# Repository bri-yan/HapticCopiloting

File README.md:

# HapticCopiloting
Codebase for UBC's ENPH-459 (Engineering Physics) Capstone Project: **Haptic Shared Control**

Demonstrating complex human-robot control through a 1 DOF haptic device featuring a BDC motor control system in live feedback with a virtual environment.

Authors: 
* Gavin Pringle
* Yousif El-Wishahy
* Sayeh Oloumi Yazdi
* Brian Yan

## Important Directories
- twiddlerino: source code for the ESP32 controller, python serial interface, unit tests and test scripts
- sim: MATLAB source code for modelling and simualtion of motor, sensors and controller
- virtual_demos : directory containing virtual demonstrations for shared control, demos implemented in pygame and interface with esp32 controller using the serial interface
- electrical: KiCad pcb project (libraries, schematics and layout) using the twiddlerino hardware, and the KiCad electrical schematic for the test bench

## Contents
 - [Project Overview](#project-overview) 
 - [Firmware Dev Environment](#firmware-dev-environment) 

## Project Overview

When dancing with a partner, forces and torques from each person influence the motion of the other. Each person’s motion is therefore partially controlled by themselves and partially controlled by their partner. 

This is similar to shared control of a robotic system, where the behaviour of a robot changes depending on the stiffness of the environment it is operating in. In our project, we explore shared control on simple robotic devices with the addition of a virtual environment that guides the user on when to give and when to take control.

### Twiddlerino System Diagram

### Control Theory

We have implemented shared control between a human and a robot by shifting between two existing controllers: impedance controllers and admittance controllers. Impedance and admittance controllers both simulate virtual spring-mass-damper systems. By shifting between these two controllers, the combined shared controller can act resistively and prevent changes to its trajectory or act compliantly and allow a person to dictate its trajectory.

### Defined Control Modes

Defined in control_type_t enum in the firmware:

| Control ID               | Description                                                                                                                                                                                                                                          |
|--------------------------|------------------------------------------------------------------------------------------------------------------------------------------------------------------------------------------------------------------------------------------------------|
| no_control               | No actuator control is applied. Only telemetry is report.                                                                                                                                                                                            |
| position                 | Position PID control. Feedback is incremental encoder signal.                                                                                                                                                                                        |
| velocity                 | Velocity PID control. Feedback is rate of change of encoder signal.                                                                                                                                                                                  |
| torque                   | Current PID control to achieve torque control, uses linear relationship between current and torque.<br>Feedback is current sensor measurements.                                                                                                      |
| impedance_spring         | Cascaded controller. Inner loop runs current control with PID. <br>Outer loop applies a spring impedance law to determine desired current. <br>The linear friction torque (scales with velocity) is also accounted for in the impedance control law. |
| impedance_damping        | Similar to imedance_spring but uses imedance damper law to compute current target.                                                                                                                                                                   |
| impedance_spring_damping | Applies spring and damping impedance law. Has the effect of position and velocity impedance control.                                                                                                                                                 |
| impedance_ignore_t_ext   | Applies full impedance law, but ignores external torques.                                                                                                                                                                                            |
| impedance                | Applies full impedance law, and accounts for external torques.<br>External torque is estimated by comparing current measurements to an internal model the motor that estimates control current.                                                      |
| admittance               | Applies full admittance law. This controller is also a cascaded controller.<br>The inner loop runs PID position control.<br>The outer loop runs an impedance control law to compute position.                                                        |

### Virtual Environment
The virtual environment guides the user on when to give and when to take control. The player  must control two twidderinos to ensure both player-controlled ships avoid all obstacles. Ships will automatically avoid asteroids but players must take action to avoid enemy projectiles.

Promoted Behaviour:
* Human-robot collaboration
* Shared common goal
* Awareness of robots actions

### Hardware Architecture

### Firmware Architecure

## Firmware Dev Environment

[Refer to firmware diagram](#firmware-architecture)

Embedded development environment: [Platformio](https://platformio.org/) IDE plugin for VSCode

[Install platformio](https://platformio.org/)

config file: `twiddlerino/platformio.ini`

Directory structure

```bash
├───.pio
│   ├───build
│   └───libdeps
├───include
├───lib
├───python_tests
│   ├───data
│   └───serial_interface
├───src
│   ├───app
│   │   ├───calibration
│   │   ├───control
│   │   └───filter
│   └───drivers
└───test
```

## Serial Commmand & Telemetry Interface

Command and telemetry of the Twiddlerino system is achieved through telemetry and command frames (utf-8 encoded strings) sent over a USB port between the ESP32 and the HOST PC.

The ESP32 devkit has an onboard CP210X USB-to-UART module that converts the USB signal to a UART signal for the UART driver on the ESP32 to handle.

The serial protocol is implemented in C++ on esp32 and Python on Host PC.

[Refer to firmware diagram for details](#firmware-architecture)

### Telemetry Definition

[Serial Studio](https://serial-studio.github.io/), an open source telemetry GUI, is used to record and visualize system data during testing of the controller.

Telemetry frames are defined in a .JSON configuration file per the serial studio standard, see `twiddlerino/serial-studio-dashboard.json`.

Telemetry frame: `"/*TWIDDLERINO_TELEMETRY,%s,%s,...,%s*/"`

The firmware running on the ESP32 periodically sends telemetry strings over a serial port. The python serial protocol recieves the telemetry frames and sends them over a TCP socket to Serial Studio. 

### Command Definition
Several commands are available to set parameters over the serial interface and to control the state of the controller.
**Each command is a newline terminated string.**

`"stop\n"` - Stops controller (telemetry also stops)

`"reset\n"` - Resets controller (configuration reverts to default)

`"reboot\n"` - Reboots the microcontroller! UART driver will not be affected.

`"telemetry_enable\n"` - Enable controller telemetry stream over serial (rate==`TELEMETRY_SAMPLES_PER_LOOP `)

`"telemetry_disable\n"` - Disable controller telemetry stream over serial (rate==`TELEMETRY_SAMPLES_PER_LOOP `)

`"set_pid,<controller_id(string)>,<double>,<double>,<double>,\n"` - Set P, I, and D values of PID controller

`"set_impedance,<controller_id(string)>,<double>,<double>,<double>,\n"` - Set stiffness, damping, and inertia values of impedane/admittance controller

`"set_mode,<controller_id(string)>,<string>,\n"` - Sets control mode, the string values represents an enum. Refer to the `control_type_t` struct definition in `twiddlerino/src/app/control/twid_control.h`.
* modes: `no_control`, `position`, `velocity`, `torque`, `impedance`, `impedance_spring`, `impedance_damping`, `impedance_spring_damping`, `impedance_ignore_t_ext`, `admittance`

`"set_setpoint,<controller_id(string)>,<double>,<double>,<double>,<double>,\n"` - Set position, velocity, acceleration and torque setpoints for the controller. 

`"set_dutycycle,<controller_id(string)>,<int>,\n"` - Sets motor duty cycle directly regardless of controller running.

`"set_telemsamplerate,<controller_id(string)>,<uint>,\n"` - Set telemetry sample rate in terms of (# control loops)/sample. I.e. how many control loops to wait before sending telemetry to serial queue.

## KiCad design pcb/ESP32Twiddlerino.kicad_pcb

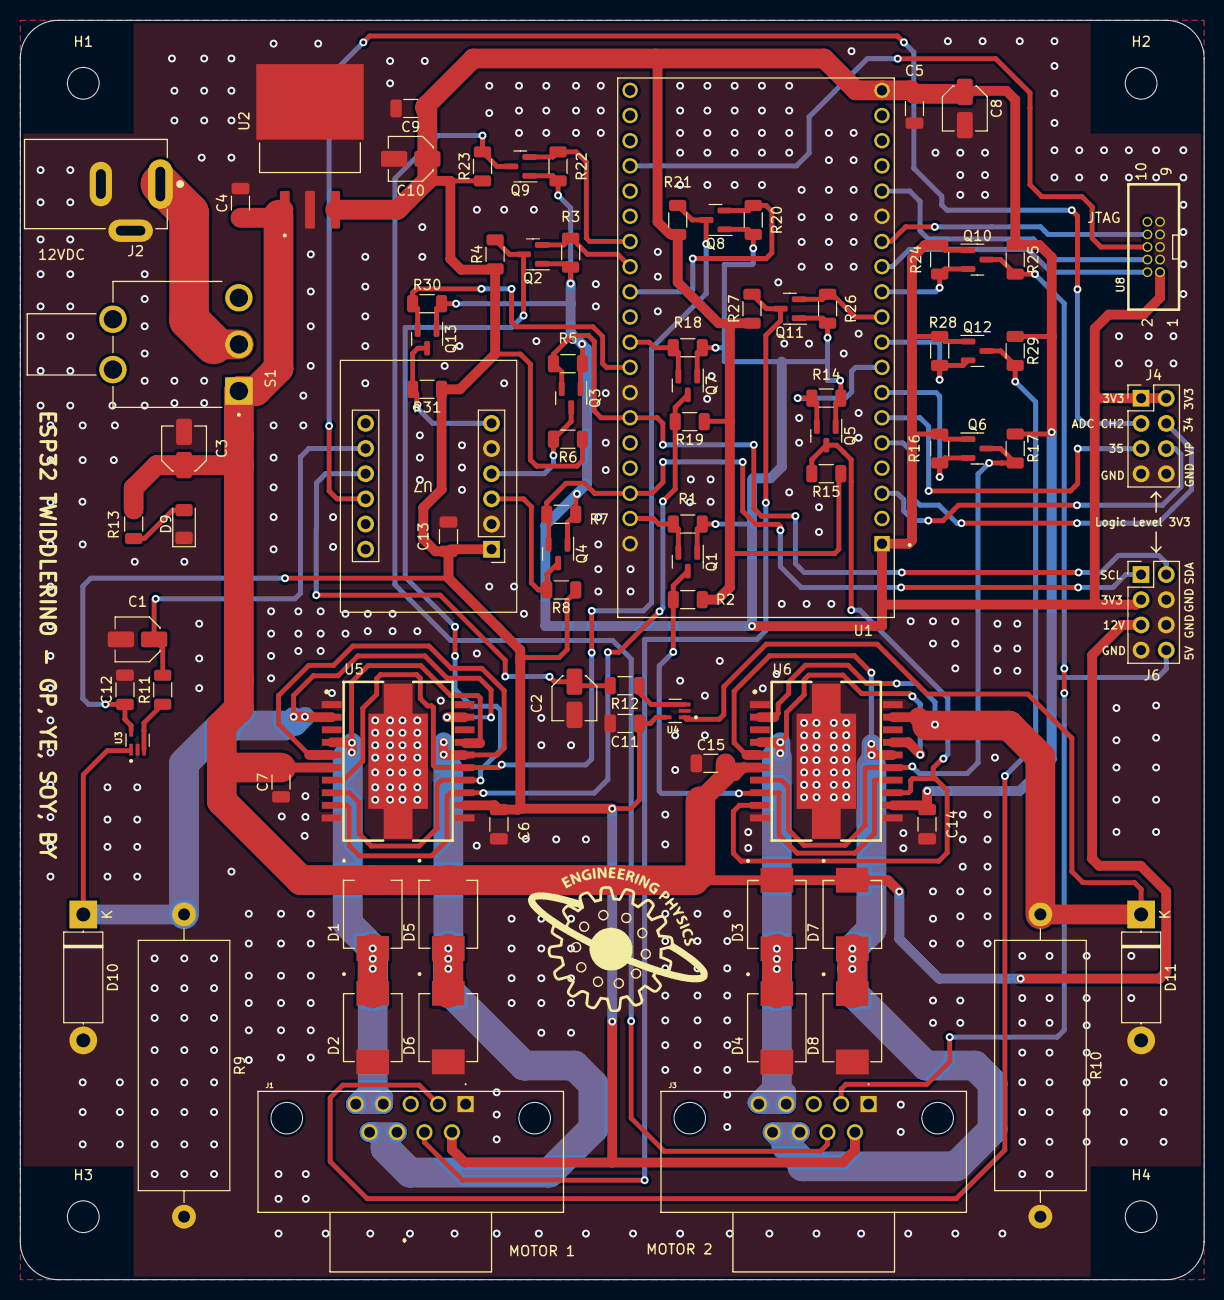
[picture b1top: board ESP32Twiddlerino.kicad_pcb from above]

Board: 2 copper layers, 119.4 x 127.0 mm, 89 parts (0 on the bottom side), 50 nets.

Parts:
.: LOGO
C1, C2: 3.3uF; C_Elec_4x5.4
C3, C8, C10: 10uF; C_Elec_4x5.4
C4: 220nF; C_1206_3216Metric
C5, C6, C7, C9, C11, C12, C13, C14, C15: 100nF; C_1206_3216Metric
D1, D2, D3, D4, D5, D6, D7, D8: RS3A; RS3A-13-F
D9: LED; LED_1206_3216Metric
D10, D11: 1N5337B; D_5W_P12.70mm_Horizontal
H1, H2, H3, H4: MountingHole; MountingHole_3.2mm_M3
J1, J3: 2311765-1; TE_2311765-1
J2: PJ-202AH; CUI_PJ-202AH
J4: Extra_GPIO; PinHeader_2x04_P2.54mm_Vertical
J6: Power_I2C; PinHeader_2x04_P2.54mm_Vertical
Q1, Q2, Q3, Q4, Q5, Q6, Q7, Q8, Q9, Q10, Q11, Q12, Q13: BSS138; SOT-23
R1, R2, R3, R4, R5, R6, R7, R8, R14, R15, R16, R17, R18, R19, R20, R21, R22, R23, R24, R25, R26, R27, R28, R29, R30, R31: 10k; R_1206_3216Metric
R9, R10: 1R; R_Axial_Power_L25.0mm_W9.0mm_P30.48mm
R11, R12: 1k; R_1206_3216Metric
R13: 470R; R_1206_3216Metric
S1: 100SP1T2B4M6QE; SW_100SP1T2B4M6QE
U1: ESP32-DEVKITC-32UE; ESPRESSIF_ESP32-DEVKITC-32UE
U2: LM340S-5.0_NOPB; LM340S-5
U3, U4: OPA347SA_3K; SOT65P210X110-5N
U5, U6: L298P
U7: adafruit_ads1115
U8: 20021511-00010T4LF

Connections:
+3.3V: J4.1, J4.2, J6.3, Q1.1 (G), Q2.1 (G), Q3.1 (G), Q4.1 (G), Q5.1 (G), Q6.1 (G), Q7.1 (G), Q8.1 (G), Q9.1 (G), Q10.1 (G), Q11.1 (G), Q12.1 (G), Q13.1 (G), R1.1, R3.1, R5.1, R7.1, R14.1, R16.1, R18.1, R20.1, R22.1, R24.1, R26.1, R28.1, R30.1, U1.1 (3V3), U8.1
+5V: C5.2, C6.2, C8.1, C9.1, C10.1, C11.1, C12.1, C13.2, C14.2, J1.6, J3.6, J6.8, R2.1, R4.1, R6.1, R8.1, R15.1, R17.1, R19.1, R21.1, R23.1, R25.1, R27.1, R29.1, R31.1, U1.19 (5V), U2.3 (OUT), U3.5 (V+), U4.5 (V+), U5.12 (VSS), U6.12 (VSS), U7.1 (Vin)
+12V: C3.1, C4.1, C7.2, C15.2, D1.C, D3.C, D5.C, D7.C, J6.5, R13.1, S1.1, U2.1 (IN), U5.6 (VS), U6.6 (VS)
ADC_ALRT_H: Q13.3 (D), R31.2, U7.6 (ALRT)
ADC_ALRT_L: Q13.2 (S), R30.2, U1.27 (19)
ESP_SCL_H: Q4.3 (D), R8.2, U7.3 (SCL)
ESP_SCL_L: J6.1, Q4.2 (S), R7.2, U1.22
ESP_SDA_H: Q3.3 (D), R6.2, U7.4 (SDA)
ESP_SDA_L: J6.2, Q3.2 (S), R5.2, U1.25 (21)
Extra_ADC_2: J4.3, U7.10 (A2)
Extra_GPIO_34: J4.4, U1.5 (34)
Extra_GPIO_35: J4.5, U1.6 (35)
Extra_GPIO_VP: J4.6, U1.3 (VP)
GND: C1.2, C2.2, C3.2, C4.2, C5.1, C6.1, C7.1, C8.2, C9.2, C10.2, C11.2, C12.2, C13.1, C14.1, C15.1, D2.A, D4.A, D6.A, D8.A, D9.1 (K), D10.2 (A), D11.2 (A), J1.1, J2.2, J2.3, J3.1, J4.7, J4.8, J6.4, J6.6, J6.7, R9.2, R10.2, U1.14 (GND), U1.20 (GND), U1.26 (GND), U2.2 (GND), U2.4 (GND), U3.2 (V-), U4.2 (V-), U5.1 (GND), U5.10 (GND), U5.11 (GND), U5.20 (GND), U5.21 (PAD), U5.22 (PAD), U5.23 (PAD), U6.1 (GND), U6.10 (GND), U6.11 (GND), U6.20 (GND), U6.21 (PAD), U6.22 (PAD), U6.23 (PAD), U7.2 (GND), U7.5 (ADDR), U8.3, U8.5, U8.7, U8.9
MTCK: U1.15 (13), U8.4
MTDI: U1.13 (12), U8.8
MTDO: U1.35 (15), U8.6
MTMS: U1.12 (14), U8.2
Mot_1_Dir_1_H: Q8.3 (D), R21.2, U5.7 (IN1), U5.15 (IN4)
Mot_1_Dir_1_L: Q8.2 (S), R20.2, U1.30 (17)
Mot_1_Dir_2_H: Q7.3 (D), R19.2, U5.9 (IN2), U5.13 (IN3)
Mot_1_Dir_2_L: Q7.2 (S), R18.2, U1.28 (18)
Mot_1_ENC_QUAD_A_H: J1.2, Q12.3 (D), R29.2
Mot_1_ENC_QUAD_A_L: Q12.2 (S), R28.2, U1.9 (25)
Mot_1_ENC_QUAD_B_H: J1.7, Q11.3 (D), R27.2
Mot_1_ENC_QUAD_B_L: Q11.2 (S), R26.2, U1.10 (26)
Mot_1_Out_A: D1.A, D2.C, J1.4, J1.5, U5.4 (OUT1), U5.17 (OUT4)
Mot_1_Out_B: D5.A, D6.C, J1.8, J1.9, U5.5 (OUT2), U5.16 (OUT3)
Mot_1_PWM_H: Q2.3 (D), R4.2, U5.8 (ENA), U5.14 (ENB)
Mot_1_PWM_L: Q2.2 (S), R3.2, U1.31 (16)
Mot_1_Sense: D10.1 (K), R9.1, U3.1 (+IN), U5.2 (SENA), U5.19 (SENB)
Mot_1_Sense_Filt: C1.1, R11.2, U7.8 (A0)
Mot_2_Dir_1_H: Q6.3 (D), R17.2, U6.7 (IN1), U6.15 (IN4)
Mot_2_Dir_1_L: Q6.2 (S), R16.2, U1.7 (32)
Mot_2_Dir_2_H: Q5.3 (D), R15.2, U6.9 (IN2), U6.13 (IN3)
Mot_2_Dir_2_L: Q5.2 (S), R14.2, U1.8 (33)
Mot_2_ENC_QUAD_A_H: J3.2, Q10.3 (D), R25.2
Mot_2_ENC_QUAD_A_L: Q10.2 (S), R24.2, U1.11 (27)
Mot_2_ENC_QUAD_B_H: J3.7, Q9.3 (D), R23.2
Mot_2_ENC_QUAD_B_L: Q9.2 (S), R22.2, U1.32 (4)
Mot_2_Out_A: D3.A, D4.C, J3.4, J3.5, U6.4 (OUT1), U6.17 (OUT4)
Mot_2_Out_B: D7.A, D8.C, J3.8, J3.9, U6.5 (OUT2), U6.16 (OUT3)
Mot_2_PWM_H: Q1.3 (D), R2.2, U6.8 (ENA), U6.14 (ENB)
Mot_2_PWM_L: Q1.2 (S), R1.2, U1.21 (23)
Mot_2_Sense: D11.1 (K), R10.1, U4.1 (+IN), U6.2 (SENA), U6.19 (SENB)
Mot_2_Sense_Filt: C2.1, R12.2, U7.9 (A1)
unnamed: D9.2 (A), R13.2
unnamed: J2.1, S1.2
unnamed: R11.1, U3.3 (-IN), U3.4 (OUT)
unnamed: R12.1, U4.3 (-IN), U4.4 (OUT)

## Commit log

2023-10-30 added basic Pong framework
2023-11-01 added pong integration
2023-12-03 Added current sensing with running average.
2023-12-10 plant implementation
2023-12-10 removed old sim files
2024-01-25 added twoway test
2024-01-31 esp32 code for twid shield interfacing and control, second core used for comms
2024-02-01 added two way test
2024-02-01 updated two way test
2024-02-01 Work in progress on force sensing via current.
2024-02-01 added prototype
2024-02-04 updates to esp32 code for testing and telemetry
2024-02-04 Current sensing rolling average implemented.
2024-02-05 Created encoder library to decode encoder signals directly on cpu as opposed to external ic, reduced io lines from 11 to 2 :)
2024-02-05 Force Sensing Finished. Plots added.
2024-02-07 firmware refactor, almost ready for testing, few more changes to make
2024-02-08 added twoway
2024-02-08 Initial command and telemetry for testing
2024-02-08 startup modes
2024-02-08 fixed build errors relating to naming of functions and undefined functions VtakGetInfo
2024-02-09 Added example ADC code to read ADC.
    Not in RTOS format! I need to learn how that works first
2024-02-11 working controller test, sending commands and receiving telemetry
2024-02-11 added current sensing from gavin's branch and refactored
2024-02-11 changed file docs
2024-03-07 fixed thresholding logic bug and motor direction bug in motor driving code, updates to telemetry code
2024-03-08 Changes made to get circuit to work in Mar 6 work session
2024-03-08 timer interrupt based controller
2024-03-09 added spaceship stuff
2024-03-09 finished updated pid controller, stop/reset over serial, more telemetry, torque estimation. All that is left is calibration and impedance,admittance switching
2024-03-09 discrete pid class
2024-03-10 current sens background task
2024-03-11 telemetry update
2024-03-11 added frame header to telemetry config
2024-03-13 initial hardware test data
2024-03-13 renamed
2024-03-13 refactor simulink files
2024-03-13 position control discrete time domain test, for tuning params
2024-03-13 added several 'set config' commands
2024-03-13 readme to describe serial commands
2024-03-14 refactoring, added additional sampling to reduce telemetry, centralized config to one file
2024-03-14 fixed reset error check causing crash
2024-03-14 updated readmes, refactor smaller readme into root readme:
2024-03-14 added 'no control' mode, and added direct set of pwm duty cycle
2024-03-14 motor speed safety check
2024-03-17 added spaceship updates
2024-03-20 game interface c (esp32) and python (pc) implementation
2024-03-20 readme
2024-03-20 gitignore vscode files
2024-03-20 pin def for encoders
2024-03-20 documenting the python serial interface
2024-03-20 game interface asyncio
2024-03-20 higher baud rate, config for output signal correction, more info in game telemetry dataclass
2024-03-21 added virtual demo integration
2024-03-21 renamed interface class and made it fully compatible with serial studio telemetry frames
2024-03-22 initial calibration curve for dc to current draw (no load)
2024-03-22 lookup file changed to source file
2024-03-22 added torque estimation using lookup table. Removed virtual env code, not used anymore.
2024-03-22 fixed comms receive bugs, added update sample rate, fixed serial interface decoding logic
2024-03-22 calibration test for determining resistance and motor constant
2024-03-27 sockets
2024-03-27 serial studio 2.0 config file
2024-03-27 motor and current sensor driver updates for new hbridge circuit
2024-03-28 remove dc fix
2024-03-28 async unit tests for telemetry
2024-03-28 Update README.md with new reboot command
2024-03-28 Socket server updates
2024-03-29 refactored test scripts
2024-03-29 gitignore
2024-03-29 updated game demo to use latest serial interface version
2024-03-29 current sensor driver changes for new lin. hall effect sensor
2024-03-29 minor code comments, and changed rpm limit + gitignore
2024-03-29 added friction estimation
2024-03-30 Additional control modes and telemetry/command support updated telem and command to support event based waits
2024-03-30 step response fit test, using regular expressions in decoding interface now
2024-03-31 current sensor firmware updates for hall sensor, added adc telemetry signal
2024-03-31 added alert adc pin to pin config
2024-03-31 current sens driver interrupt and telem script update
2024-03-31 config i2c clock after bus init
2024-04-01 renamed filed to better rep purpose, also added comments for control references
2024-04-01 current step response system identification
2024-04-01 system identification test changed so initial dead time guess is 0
2024-04-02 reference tracking test
2024-04-02 added single twid control
2024-04-02 added new demo
2024-04-04 logging, better curve fitting, set multi setpoint cmd
2024-04-04 collect_telem now returns pandas dataframe, tested test scripts in jupyter notebook
2024-04-04 added extensive logging to esp32
2024-04-05 minor logging changes and added reboot test
2024-04-05 removed unused init config in firmware, better logging across all firmware modules, removed setpoint buffer causing memory leaks
2024-04-05 renamed serial test
2024-04-05 rebased hardware driver changes onto logger changes
2024-04-05 serial interface and test support for two twids
2024-04-05 firmware support for two different control loops
2024-04-05 tested telem for 2 twids
2024-04-05 swapped encoder pin definitions to match test board
2024-04-05 calibration and config changes made during testing, see test logs for details
2024-04-06 transfer function for position and velocity obtained
2024-04-06 pulled in latest virtual demos and refactored
2024-04-07 updated and tested game demos to use latest interface
2024-04-07 readme changes and added pcb
2024-04-07 ignore logs
2024-04-07 added spring demo
2024-04-07 [WIP]initial internal adc driver code w/ dma, not working yet, just wip commit
2024-04-07 added support for two twiddlerinos
2024-04-07 updated controllers
2024-04-07 Add files via upload
    Most recent version of switching between admittance and impedance control
2024-04-07 variable impedance added
2024-04-07 added score
2024-04-08 added game over screen
2024-04-08 added admittance
2024-04-08 working but not fast
2024-04-08 added channels
2024-04-08 ported over firmware from arduino-esp32 to pure espidf, updated all hardware drivers, and added adc continous driver
2024-04-09 added test bench schematic and component libs
2024-04-09 updated schematic title and added pdf
2024-04-09 Added pdf of PCB schematic
2024-04-09 added command executor to serial interface
2024-04-09 fixed some minor bugs related to motor driver
2024-04-09 Update README.md for task designation
